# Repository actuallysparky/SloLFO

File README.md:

# SloLFO

SloLFO is an 8 HP slow Eurorack LFO module and a VCV Rack 2 plugin. The VCV plugin is availalbe prior to the eurorack module and is being used as an exploring ground for the user interface. Three phase-aligned outputs provide sine, triangle, and square CV. The module uses one push encoder and an 8×8 color matrix modeled on the Waveshare RP2350-Matrix hardware fork.

**Author for the VCV plugin: Bearamin.** Inspired by Patience, with thanks to the wonders of slow time.

## Try the VCV module

| Action | Result |
| --- | --- |
| Tap the encoder for under 0.5 seconds | Select Minutes, Hours, Days, or Months; the selected 4×4 color quadrant is bright. |
| Turn the encoder | Set 1–60 minutes, 1–24 hours, 1–64 days in half-day steps, or 1–64 fixed 30-day months. |
| Hold for 0.5 seconds | Preview the present voltage mode: four blue upper rows for 0–5 V, or blue upper and red lower rows for −5–5 V. |
| Continue holding to 2 seconds | Switch all three outputs immediately and update the preview; a longer hold does not switch again. |

Minutes and Hours show period as a colored pie. Days and Months fill the grid from the upper left, one pixel per day or month; half-day settings half-light the next pixel. At idle, a colored triangle remains static while one bright pixel follows phase. Its upper-half shape indicates unipolar output; bipolar uses the display's full height. The three CV outputs remain active together.

The plugin is a user-experience prototype. A fixed month is 30 days, so the longest setting is 1,920 days. The included firmware now targets the RP2350/8×8 module and follows the same front-panel controls and displays. Physical behavior remains to be checked on an assembled module.

## Contents

- [`vcv/`](vcv/) — Rack plugin C++ source, panel SVG, manifest, build files, and panel generator.
- [`firmware/`](firmware/) — RP2350/8×8 firmware source, local board definition, and build instructions.
- [`hardware/`](hardware/) — RP2350 carrier and 8×8 faceplate KiCad PCB files plus the custom footprints they use.
- [`bom/`](bom/) — a current board-derived parts list and an older priced Rev B workbook, with revision notes.
- [`docs/functional-spec.md`](docs/functional-spec.md) — proposed behavior and electrical architecture.
- [`docs/2350-fork-notes.md`](docs/2350-fork-notes.md) — RP2350 pin mapping and open hardware issues.

## Build the Rack plugin

Install the VCV Rack 2 plugin SDK and set `RACK_DIR` to its extracted `Rack-SDK` directory. The checked-in panel SVG lets a normal plugin build use the existing artwork; regenerating it from the faceplate requires KiCad's `kicad-cli` and Python 3.

```sh
cd vcv
make RACK_DIR=/absolute/path/to/Rack-SDK
make dist RACK_DIR=/absolute/path/to/Rack-SDK
```

The `.vcvplugin` package appears under `vcv/dist/`. The plugin manifest uses the `SlowLFOPrototype` slug and `Bearamin` author. The checked-in panel SVG is packaged as-is; run `make -C vcv panel` when the KiCad faceplate changes.

For a release package built from the current committed source, run:

```sh
RACK_DIR=/absolute/path/to/Rack-SDK ./vcv/build_release.sh
```

This uses `git archive HEAD` in a temporary directory, builds with the supplied Rack 2 SDK, and writes the plugin archive plus a SHA-256 checksum to `_local/releases/v2.0.6/`. Use a Rack 2.6.6 SDK for the current release. The script requires a clean tracked tree so the resulting package can be tied to a commit. The `.vcvplugin` contains `plugin.json`, the panel artwork, and the GPL license; the separate RP2350 firmware is not part of the Rack package.

The manually triggered [cross-platform release workflow](.github/workflows/release-cross-platform.yml) builds Windows x64 and Linux x64 packages from the fixed `v2.0.6` tag with their matching Rack 2.6.6 SDKs, checks package contents, and attaches packages, checksums, and build details to the private GitHub release. The macOS ARM64 package is built with the local release script above.

On macOS systems whose default Command Line Tools SDK reports an `arm64e.x1` linker error, set `SDKROOT` to a compatible Xcode SDK. This release was built with `SDKROOT=/Applications/Xcode.app/Contents/Developer/Platforms/MacOSX.platform/Developer/SDKs/MacOSX26.5.sdk`. The script also writes `BUILDINFO.txt` with the source commit, SDK, compiler, and platform used.

## License and project status

SloLFO is licensed under [GPL-3.0-or-later](LICENSE), the license identifier used by [VCV Core](https://github.com/VCVRack/Rack/blob/v2/Core.json). TUpdates to the plugin, firmware, and boards will be published here as the design evolves. See the [firmware build and pin map](firmware/README.md) and [hardware files](hardware/README.md).

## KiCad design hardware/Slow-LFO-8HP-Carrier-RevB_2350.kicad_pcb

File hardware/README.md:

# Hardware

`Slow-LFO-8HP-Carrier-RevB_2350.kicad_pcb` and `Slow-LFO-8HP-Faceplate_8x8.kicad_pcb` are the RP2350/8×8 carrier and faceplate designs. `SlowLFO.pretty` contains the custom footprints referenced by the carrier, and `fp-lib-table` points KiCad to that directory.

The boards are the current design files in this private development repository. The carrier has open electrical and fit work; fabrication and validation are the next hardware milestones. See [RP2350 fork notes](../docs/2350-fork-notes.md) and the [functional specification](../docs/functional-spec.md) for the pin map and circuit design.

Open either PCB in KiCad to inspect or continue the layout. The matching RP2350 firmware source is in `../firmware/`.

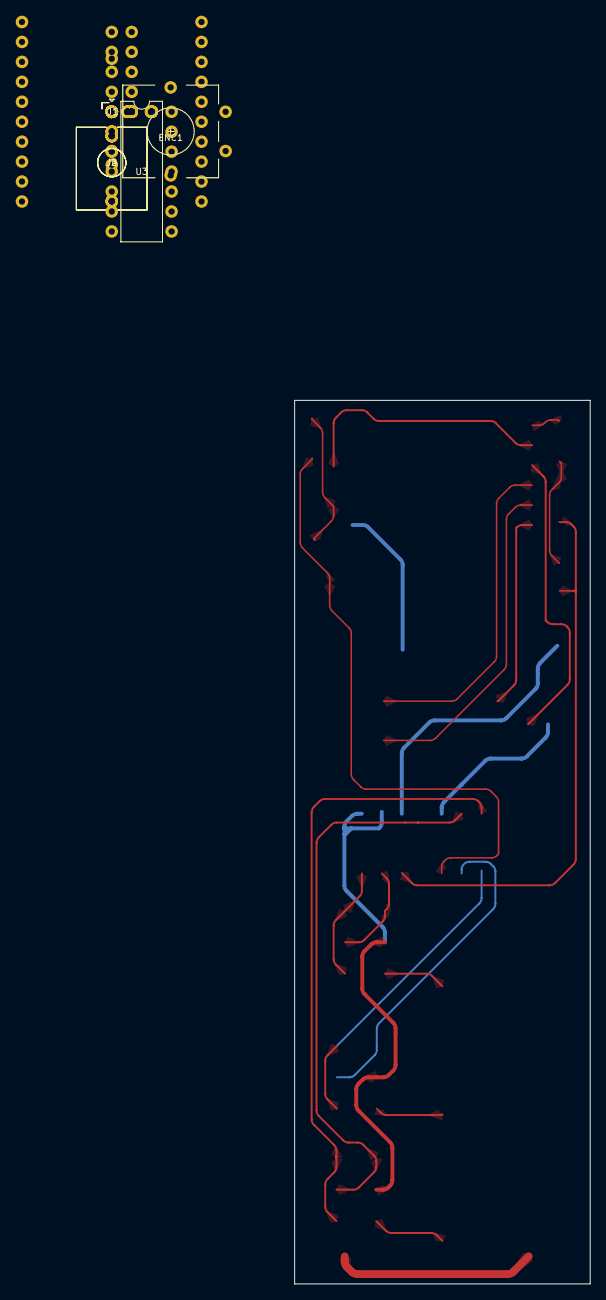
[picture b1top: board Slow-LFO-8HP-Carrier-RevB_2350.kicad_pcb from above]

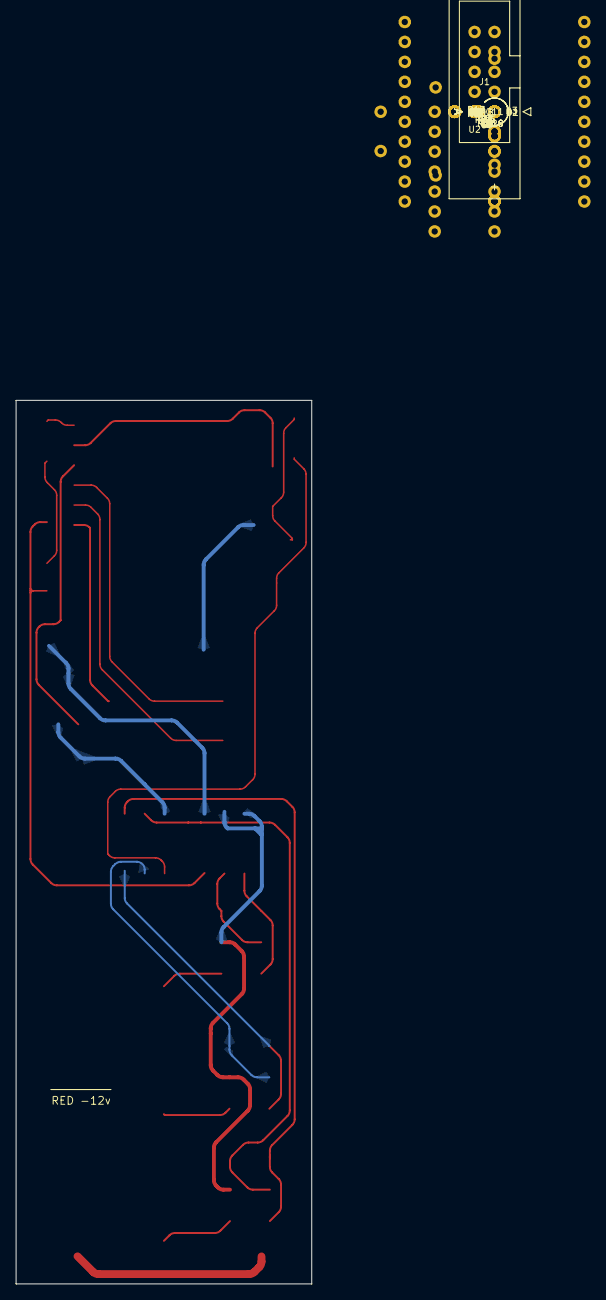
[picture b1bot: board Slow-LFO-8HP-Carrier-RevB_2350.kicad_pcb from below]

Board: 4 copper layers, 37.6 x 112.5 mm, 41 parts (35 on the bottom side), 32 nets.

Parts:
C2, C3, C4, C5, C8: 10uF; CP_Radial_D5.0mm_P2.00mm_CenterLabel
C6, C7: 100nF; C_Disc_D5.0mm_W2.5mm_P5.00mm_CenterLabel
C9: 2u2 X7R 25V; C410_Aximax_Axial_Vertical_P2.50mm_HandFormed
C11: 0.33F 9V; SCMR14L334SRBB0
D1, D2, D3: 1N5819; D_DO-41_SOD81_P2.54mm_Vertical_AnodeUp
ENC1: A/B/C plus switch; RotaryEncoder_Alps_EC11E-Switch_Vertical_H20mm_CircularMoun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
J1: 10pin IDC keyed; IDC-Header_2x05_P2.54mm_Latch_Vertical
J2: Jack_3.5mm_QingPu_WQP-PJ398SM_Vertical_CircularHo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; Jack_3.5mm_QingPu_WQP-PJ398SM_Vertical_CircularHoles_J2
J3: Jack_3.5mm_QingPu_WQP-PJ398SM_Vertical_CircularHo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; Jack_3.5mm_QingPu_WQP-PJ398SM_Vertical_CircularHoles_J3
J4: Jack_3.5mm_QingPu_WQP-PJ398SM_Vertical_CircularHo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; Jack_3.5mm_QingPu_WQP-PJ398SM_Vertical_CircularHoles_J4
R1, R2, R6, R7: 3k3; R_Axial_DIN0207_L6.3mm_D2.5mm_P5.08mm_Vertical_CenterLabel
R3, R8, R11: 12k; R_Axial_DIN0207_L6.3mm_D2.5mm_P5.08mm_Vertical_CenterLabel
R4, R9, R12: 5k76; R_Axial_DIN0207_L6.3mm_D2.5mm_P5.08mm_Vertical_CenterLabel
R5, R10, R13: 330R; R_Axial_DIN0207_L6.3mm_D2.5mm_P5.08mm_Vertical_CenterLabel
R14: 10k5; R_Axial_DIN0207_L6.3mm_D2.5mm_P2.54mm_Vertical_CenterLabel
R15: 30k1; R_Axial_DIN0207_L6.3mm_D2.5mm_P2.54mm_Vertical_CenterLabel
R16: 3k3; R_Axial_DIN0207_L6.3mm_D2.5mm_P2.54mm_Vertical_CenterLabel
R18: 10R >=3W pulse; ChargeResistor_3W
R19, R20, R21, R22: 10k; R_Axial_DIN0207_L6.3mm_D2.5mm_P2.54mm_Vertical_CenterLabel
U1: RP2350-Matrix; RP2350-Matrix_8x8_THT
U2: R-78B5.0-1.0; RECOM_R78B5.0_Rear
U3: TL074; DIP-14_W7.62mm

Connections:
3V3: R14.1, U1.3
+5V_BUCK: D1.1, D2.1, R19.1, U2.3
+12V: C6.1, C8.1, J1.9, J1.10, U2.1, U3.4
-12V: C7.1, J1.1, J1.2, U3.11
BUCK_SENSE: R19.2, R20.1, U1.7
CAP+: C11.1, D3.1, R18.2, R21.1
CAP_SENSE: R21.2, R22.1, U1.6
CHARGE_IN: D2.2, R18.1
ENC_A: ENC1.A, U1.14
ENC_B: ENC1.B, U1.15
ENC_SW: ENC1.S2, U1.16
GND: C2.2, C3.2, C4.2, C5.2, C6.2, C7.2, C8.2, C9.2, C11.2, ENC1.C, ENC1.S1, J1.3, J1.4, J1.5, J1.6, J1.7, J1.8, J2.S, J3.S, J4.S, R15.2, R20.2, R22.2, U1.2, U2.2
PWM_SINE: R1.1, U1.11
PWM_SQUARE: R16.1, U1.13
PWM_TRI: R6.1, U1.12
REF_DIV: R14.2, R15.1, U3.12
SINE_BUF: R3.1, R5.1, U3.1
SINE_F1: C2.1, R1.2, R2.1
SINE_F2: C3.1, R2.2, U3.3
SINE_NFB: R3.2, R4.1, U3.2
SINE_OUT: J2.T, R5.2
SQUARE_BUF: R11.1, R13.1, U3.8
SQUARE_F1: C9.1, R16.2, U3.10
SQUARE_NFB: R11.2, R12.1, U3.9
SQUARE_OUT: J4.T, R13.2
TRI_BUF: R8.1, R10.1, U3.7
TRI_F1: C4.1, R6.2, R7.1
TRI_F2: C5.1, R7.2, U3.5
TRI_NFB: R8.2, R9.1, U3.6
TRI_OUT: J3.T, R10.2
VREF_2V45: R4.2, R9.2, R12.2, U3.13, U3.14
VSYS: D1.2, D3.2, U1.1

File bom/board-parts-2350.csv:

"Refs","Value","Footprint","Qty","DNP"
"C2","10uF","SlowLFO:CP_Radial_D5.0mm_P2.00mm_CenterLabel","1",""
"C3","10uF","SlowLFO:CP_Radial_D5.0mm_P2.00mm_CenterLabel","1",""
"C4","10uF","SlowLFO:CP_Radial_D5.0mm_P2.00mm_CenterLabel","1",""
"C5","10uF","SlowLFO:CP_Radial_D5.0mm_P2.00mm_CenterLabel","1",""
"C6","100nF","SlowLFO:C_Disc_D5.0mm_W2.5mm_P5.00mm_CenterLabel","1",""
"C7","100nF","SlowLFO:C_Disc_D5.0mm_W2.5mm_P5.00mm_CenterLabel","1",""
"C8","10uF","SlowLFO:CP_Radial_D5.0mm_P2.00mm_CenterLabel","1",""
"C9","2u2 X7R 25V","SlowLFO:C410_Aximax_Axial_Vertical_P2.50mm_HandFormed","1",""
"C11","0.33F 9V","SlowLFO:SCMR14L334SRBB0","1",""
"D1","1N5819","Diode_THT:D_DO-41_SOD81_P2.54mm_Vertical_AnodeUp","1",""
"D2","1N5819","Diode_THT:D_DO-41_SOD81_P2.54mm_Vertical_AnodeUp","1",""
"D3","1N5819","Diode_THT:D_DO-41_SOD81_P2.54mm_Vertical_AnodeUp","1",""
"ENC1","A/B/C plus switch","Rotary_Encoder:RotaryEncoder_Alps_EC11E-Switch_Vertical_H20mm_CircularMountingHoles","1",""
"J1","10pin IDC keyed","Connector_IDC:IDC-Header_2x05_P2.54mm_Latch_Vertical","1",""
"J2","Jack_3.5mm_QingPu_WQP-PJ398SM_Vertical_CircularHoles","SlowLFO:Jack_3.5mm_QingPu_WQP-PJ398SM_Vertical_CircularHoles_J2","1",""
"J3","Jack_3.5mm_QingPu_WQP-PJ398SM_Vertical_CircularHoles","SlowLFO:Jack_3.5mm_QingPu_WQP-PJ398SM_Vertical_CircularHoles_J3","1",""
"J4","Jack_3.5mm_QingPu_WQP-PJ398SM_Vertical_CircularHoles","SlowLFO:Jack_3.5mm_QingPu_WQP-PJ398SM_Vertical_CircularHoles_J4","1",""
"R1","3k3","SlowLFO:R_Axial_DIN0207_L6.3mm_D2.5mm_P5.08mm_Vertical_CenterLabel","1",""
"R2","3k3","SlowLFO:R_Axial_DIN0207_L6.3mm_D2.5mm_P5.08mm_Vertical_CenterLabel","1",""
"R3","12k","SlowLFO:R_Axial_DIN0207_L6.3mm_D2.5mm_P5.08mm_Vertical_CenterLabel","1",""
"R4","5k76","SlowLFO:R_Axial_DIN0207_L6.3mm_D2.5mm_P5.08mm_Vertical_CenterLabel","1",""
"R5","330R","SlowLFO:R_Axial_DIN0207_L6.3mm_D2.5mm_P5.08mm_Vertical_CenterLabel","1",""
"R6","3k3","SlowLFO:R_Axial_DIN0207_L6.3mm_D2.5mm_P5.08mm_Vertical_CenterLabel","1",""
"R7","3k3","SlowLFO:R_Axial_DIN0207_L6.3mm_D2.5mm_P5.08mm_Vertical_CenterLabel","1",""
"R8","12k","SlowLFO:R_Axial_DIN0207_L6.3mm_D2.5mm_P5.08mm_Vertical_CenterLabel","1",""
"R9","5k76","SlowLFO:R_Axial_DIN0207_L6.3mm_D2.5mm_P5.08mm_Vertical_CenterLabel","1",""
"R10","330R","SlowLFO:R_Axial_DIN0207_L6.3mm_D2.5mm_P5.08mm_Vertical_CenterLabel","1",""
"R11","12k","SlowLFO:R_Axial_DIN0207_L6.3mm_D2.5mm_P5.08mm_Vertical_CenterLabel","1",""
"R12","5k76","SlowLFO:R_Axial_DIN0207_L6.3mm_D2.5mm_P5.08mm_Vertical_CenterLabel","1",""
"R13","330R","SlowLFO:R_Axial_DIN0207_L6.3mm_D2.5mm_P5.08mm_Vertical_CenterLabel","1",""
"R14","10k5","SlowLFO:R_Axial_DIN0207_L6.3mm_D2.5mm_P2.54mm_Vertical_CenterLabel","1",""
"R15","30k1","SlowLFO:R_Axial_DIN0207_L6.3mm_D2.5mm_P2.54mm_Vertical_CenterLabel","1",""
"R16","3k3","SlowLFO:R_Axial_DIN0207_L6.3mm_D2.5mm_P2.54mm_Vertical_CenterLabel","1",""
"R18","10R >=3W pulse","SlowLFO:ChargeResistor_3W","1",""
"R19","10k","SlowLFO:R_Axial_DIN0207_L6.3mm_D2.5mm_P2.54mm_Vertical_CenterLabel","1",""
"R20","10k","SlowLFO:R_Axial_DIN0207_L6.3mm_D2.5mm_P2.54mm_Vertical_CenterLabel","1",""
"R21","10k","SlowLFO:R_Axial_DIN0207_L6.3mm_D2.5mm_P2.54mm_Vertical_CenterLabel","1",""
"R22","10k","SlowLFO:R_Axial_DIN0207_L6.3mm_D2.5mm_P2.54mm_Vertical_CenterLabel","1",""
"U1","RP2350-Matrix","SlowLFO:RP2350-Matrix_8x8_THT","1",""
"U2","R-78B5.0-1.0","SlowLFO:RECOM_R78B5.0_Rear","1",""
"U3","TL074","Package_DIP:DIP-14_W7.62mm","1",""

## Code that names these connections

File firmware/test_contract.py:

#!/usr/bin/env python3
"""Focused source contract for the RP2350 SloLFO control and recovery path."""

from pathlib import Path


ROOT = Path(__file__).resolve().parents[1]
SOURCE = (ROOT / "firmware" / "main.cpp").read_text()
BOARD = (ROOT / "firmware" / "boards" / "slow_lfo_rp2350_matrix.h").read_text()
CMAKE = (ROOT / "firmware" / "CMakeLists.txt").read_text()


def between(start: str, end: str) -> str:
    first = SOURCE.index(start)
    return SOURCE[first:SOURCE.index(end, first)]


assert "pico_board_cmake_set(PICO_PLATFORM, rp2350)" in BOARD
assert "PICO_DEFAULT_WS2812_PIN 25" in BOARD
assert "set(PICO_BOARD slow_lfo_rp2350_matrix" in CMAKE
assert "constexpr uint PWM_SINE = 10, PWM_TRI = 11, PWM_SQUARE = 12;" in SOURCE
assert "constexpr uint ENC_A = 13, ENC_B = 14, ENC_PUSH = 15;" in SOURCE
assert "constexpr uint BUCK_ADC = 26, CAP_ADC = 27, LED_PIN = 25;" in SOURCE
assert "constexpr uint64_t MONTH_US = 30ULL * DAY_US;" in SOURCE
assert "constexpr uint64_t PERIOD_MIN_US = 60ULL * SECOND_US;" in SOURCE
assert "constexpr uint64_t PERIOD_MAX_US = 64ULL * MONTH_US;" in SOURCE
assert "constexpr uint64_t STEP_US[4] = {60ULL * SECOND_US, 3600ULL * SECOND_US, DAY_US / 2, MONTH_US};" in SOURCE

encoder = between("struct Encoder", "} // namespace")
assert "if (!reserve_ready || power_failed)" in encoder
assert "press_eligible=false;" in encoder and "mode_hold_preview=false;" in encoder
assert "mode_hold_preview=held>=500000;" in encoder
assert "if (held>=2000000 && !mode_switched)" in encoder
assert "if (pressed) {turned_during_press=true; mode_hold_preview=false;}" in encoder
assert "selected_unit=(selected_unit+1)%4;" in encoder

main = SOURCE[SOURCE.index("int main()") :]
assert "next_sample=now+2000;" in main
assert "next_wave=now+10000;" in main
assert main.index("blank();") < main.index("append_record(time_us_64(),true)")
assert "cap_mv>=CAP_READY_MV && buck_mv>=BUCK_RECOVER_MV" in main
assert "if (reserve_ready && cap_mv<CAP_READY_HYST_MV)" in main
assert "outputs(reserve_ready?phase_at(now):base_phase);" in main
assert "remainder=(now-anchor_us)%period_us;" in SOURCE

print("RP2350 SloLFO timing, reserve, and encoder contracts passed")
